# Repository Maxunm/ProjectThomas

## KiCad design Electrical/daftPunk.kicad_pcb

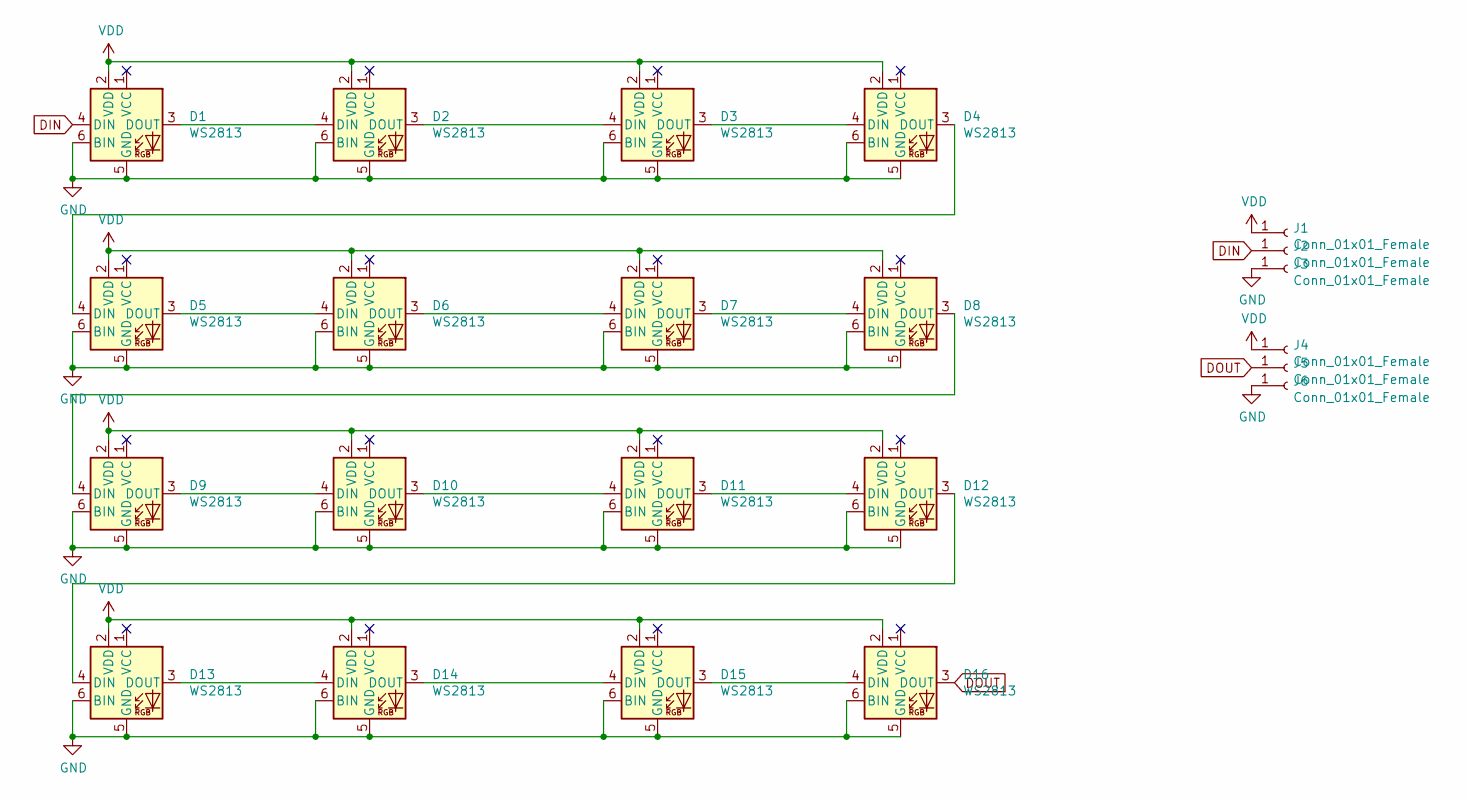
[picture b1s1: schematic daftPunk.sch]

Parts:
D1, D2, D3, D4, D5, D6, D7, D8, D9, D10, D11, D12, D13, D14, D15, D16: WS2813; LED_WS2812_PLCC6_5.0x5.0mm_P1.6mm
J1, J2, J3, J4, J5, J6: Conn_01x01_Female; TestPoint_Pad_1.5x1.5mm

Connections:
DIN: D1.4 (DIN), J2.1
DOUT: D16.3 (DOUT), J5.1
GND: D1.5 (GND), D1.6 (BIN), D2.5 (GND), D2.6 (BIN), D3.5 (GND), D3.6 (BIN), D4.5 (GND), D4.6 (BIN), D5.5 (GND), D5.6 (BIN), D6.5 (GND), D6.6 (BIN), D7.5 (GND), D7.6 (BIN), D8.5 (GND), D8.6 (BIN), D9.5 (GND), D9.6 (BIN), D10.5 (GND), D10.6 (BIN), D11.5 (GND), D11.6 (BIN), D12.5 (GND), D12.6 (BIN), D13.5 (GND), D13.6 (BIN), D14.5 (GND), D14.6 (BIN), D15.5 (GND), D15.6 (BIN), D16.5 (GND), D16.6 (BIN), J3.1, J6.1
unnamed: D1.3 (DOUT), D2.4 (DIN)
unnamed: D2.3 (DOUT), D3.4 (DIN)
unnamed: D3.3 (DOUT), D4.4 (DIN)
unnamed: D4.3 (DOUT), D5.4 (DIN)
unnamed: D5.3 (DOUT), D6.4 (DIN)
unnamed: D6.3 (DOUT), D7.4 (DIN)
unnamed: D7.3 (DOUT), D8.4 (DIN)
unnamed: D8.3 (DOUT), D9.4 (DIN)
unnamed: D10.3 (DOUT), D11.4 (DIN)
unnamed: D9.3 (DOUT), D10.4 (DIN)
unnamed: D11.3 (DOUT), D12.4 (DIN)
unnamed: D12.3 (DOUT), D13.4 (DIN)
unnamed: D13.3 (DOUT), D14.4 (DIN)
unnamed: D14.3 (DOUT), D15.4 (DIN)
unnamed: D15.3 (DOUT), D16.4 (DIN)
VDD: D1.2 (VDD), D2.2 (VDD), D3.2 (VDD), D4.2 (VDD), D5.2 (VDD), D6.2 (VDD), D7.2 (VDD), D8.2 (VDD), D9.2 (VDD), D10.2 (VDD), D11.2 (VDD), D12.2 (VDD), D13.2 (VDD), D14.2 (VDD), D15.2 (VDD), D16.2 (VDD), J1.1, J4.1

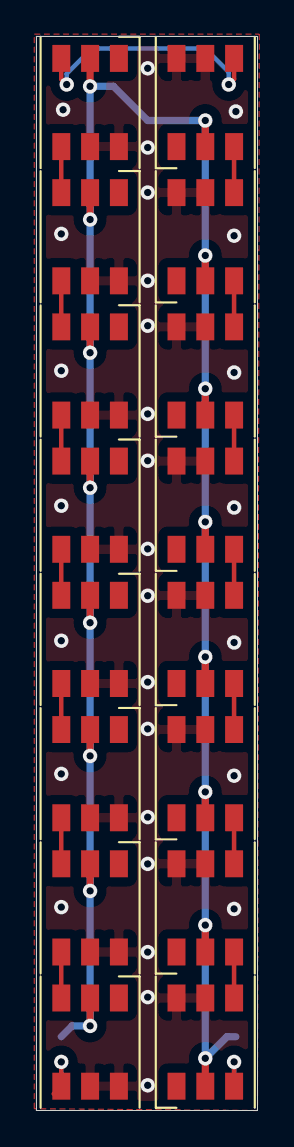
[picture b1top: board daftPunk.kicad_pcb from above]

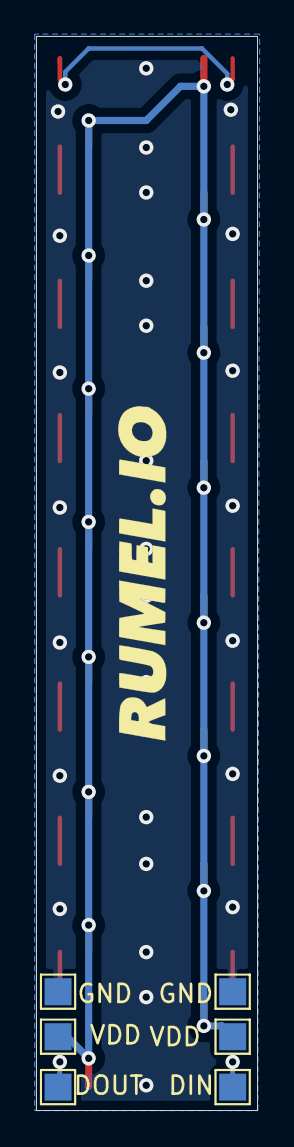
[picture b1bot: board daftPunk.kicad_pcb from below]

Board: 2 copper layers, 12.3 x 59.7 mm, 22 parts (6 on the bottom side), 19 nets.

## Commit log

2020-08-06 Initial Electrical commit
2020-08-06 Added Code/led.py
2020-08-06 PCB updated to only have pads for board interconnect
2020-08-07 Exported .step of PCB
2020-08-07 added render
2020-08-07 Sent pcb for assembly review
2020-08-07 Added New LED Matrix Classes and json functionality
2020-08-07 Different animation storage methods
2020-08-10 Added .dat compression as default method
2020-08-10 Cleaned up ledMatrix.py
2020-08-10 LEDs can reference thier own LED number
2020-08-10 Added comments to ledMatrix.py
2020-08-10 Missing parenthese fixed
2020-08-11 Added some comments and a decoder for dat files
